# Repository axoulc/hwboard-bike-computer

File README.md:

# HWBoard Bike Computer PCB

This repository contains the KiCad hardware design for an open-source bike computer PCB. The target design is a solderable, small-series-friendly board with a sunlight-readable display, dual-frequency GNSS, BLE/ANT+ radio support, local storage, outdoor sensors, and USB-C rechargeable Li-ion power.

The hardware direction is based on a Rust `no_std` firmware target using `embassy-stm32`.

## Hardware Architecture

```text
USB-C 5 V
   |
   +-- ESD protection / CC resistors
   |
BQ25622E Li-ion charger with power path
   |
   +-- 1S Li-ion battery + NTC
   +-- SYS rail
   +-- I2C to STM32
        |
        +-- 3V3 system rail
        +-- low-noise GNSS rail
        +-- filtered radio rail
        +-- sensor rail
        +-- display backlight driver

STM32H563VIT6
   +-- SPI TFT display
   +-- I2C touch / sensors / power management
   +-- u-blox NEO-F10N GNSS over UART
   +-- nRF52840 module over SPI
   +-- microSD over SDMMC 4-bit
   +-- USB FS optional
   +-- SWD debug
```

## Main Components

| Function | Selected or target part | Notes |
|---|---|---|
| MCU | `STM32H563VIT6` | Cortex-M33, 250 MHz, 2 MB flash, 640 KB RAM, LQFP100 |
| GNSS | `u-blox NEO-F10N` | Dual-frequency L1/L5 GNSS with external active antenna |
| Radio | Raytac `MDBT50Q-U1MV2` module | nRF52840 module candidate with U.FL connector for an external antenna |
| Charger / power path | `BQ25622E` / `BQ25622ERYKR` | 1S Li-ion, USB-C input, I2C control |
| Fuel gauge | `MAX17048G+` | ModelGauge battery SoC monitor over I2C |
| Boost converter | `TPS61089` | High-current boost converter for auxiliary rails |
| IMU | `LSM6DSVTR` | 6-axis accelerometer + gyroscope |
| Magnetometer | `LIS2MDLTR` | Keep away from inductors, speaker/haptic parts, battery current, USB-C, and steel hardware |
| Barometer | `LPS22DFTR` preferred, `LPS22HBTR` acceptable | New design should prefer LPS22DF; include a vent and hydrophobic membrane |
| Storage | microSD | SDMMC 4-bit interface |
| Display | 2.8-3.0 inch 240x400 SPI TFT target | Final outdoor transflective panel still to be confirmed |

## Design Priorities

- No BGA packages for the main board.
- External antennas through U.FL / I-PEX MHF connectors.
- Keep GNSS, radio, magnetometer, switching converters, and backlight physically separated.
- Use a compact, well-controlled power layout around charger and boost switch nodes.
- Keep the display SPI bandwidth realistic by using partial redraws and DMA.
- Include physical buttons because touch can be unreliable with rain, gloves, or vibration.

## Documentation

Local component datasheets are kept in [docs/datasheets](docs/datasheets). The index in [docs/README.md](docs/README.md) records each local PDF and the official source URL.

Current local datasheets include:

- `STM32H563VI`
- `NEO-F10N`
- `MDBT50Q-U1MV2`
- `BQ25622E`
- `TPS61089`
- `LIS2MDL`
- `LSM6DSV`
- `LPS22DF`

The `MAX17048/MAX17049` datasheet is linked from the docs index through Analog Devices because the official PDF endpoint did not complete an unattended download in this environment.

## Preview

### Schematics

[Fullscreen PDF](https://axoulc.github.io/hwboard-bike-computer/assets/schematics/hwboard-bike-computer-schematic.pdf)

### PCB

#### Top

#### Bottom

### 3D

## Manufacturing

This project uses KiBot automation to generate manufacturing files:

- Schematics in PDF and PNG
- PCB documentation in PDF and PNG
- Bill of materials in HTML, XLSX, and interactive formats
- Gerbers, drill files, and position files
- 3D models and renders

See [KIBOT_CICD.md](KIBOT_CICD.md) for details.

## Sponsor

Thanks to PCBWay for sponsoring fabrication and assembly of the hwboard-bike-computer prototype.

## License

This project is licensed under the CERN Open Hardware Licence Version 2 - Permissive.

For more details, see <https://ohwr.org/project/cernohl/wikis/Documents/CERN-OHL-version-2>.

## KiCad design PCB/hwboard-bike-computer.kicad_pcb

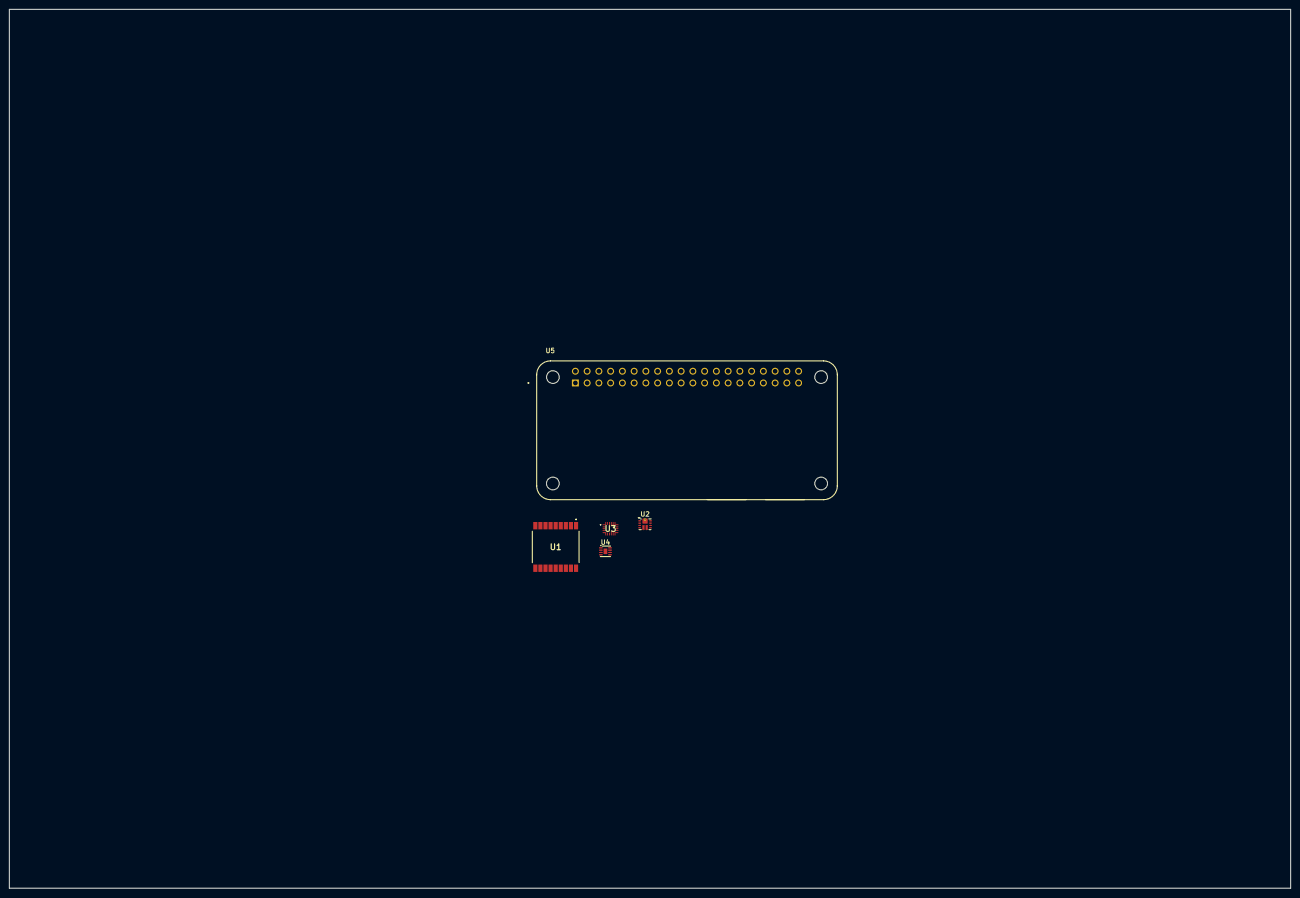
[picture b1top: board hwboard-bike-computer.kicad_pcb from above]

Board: 2 copper layers, 277.0 x 190.0 mm, 5 parts (0 on the bottom side), 6 nets, no tracks yet.

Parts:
U1: TESEO-LIV3R; TESEOLIV3R
U2: TPS61089; Texas_VQFN-RNR0011A-11
U3: BQ25622ERYKR
U4: MAX17048G+; TDFN-8-1EP_2x2mm_P0.5mm_EP0.8x1.2mm
U5: RASPBERRY_PI_ZERO_2_W; MODULE_RASPBERRY_PI_ZERO_2_W

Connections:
/CPU/3V3_{OUT}: U5.1 (3V3_1), U5.17 (3V3_17)
/CPU/5V_{IN}: U5.2 (5V_2), U5.4 (5V_4)
/Power Management/V_{BATT}: U3.8 (BAT), U4.2 (CELL), U4.3 (VDD)
/Power Management/V_{LOAD}: U2.9 (VIN), U3.9 (SYS)
GND: U1.1 (GND), U1.10 (GND_{RF}), U1.12 (GND_{RF}), U2.5 (GND), U3.15 (GND), U4.1 (CTG), U4.4 (GND), U4.6 (QSTRT), U4.9 (EP), U5.6 (GND_6), U5.9 (GND_9), U5.14 (GND_14), U5.20 (GND_20), U5.25 (GND_25), U5.30 (GND_30), U5.34 (GND_34), U5.39 (GND_39)
unnamed: U1.6 (V_{BATT}), U1.7 (VCC_{IO}), U1.8 (VCC)

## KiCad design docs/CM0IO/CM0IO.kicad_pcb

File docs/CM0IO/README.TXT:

These files have been created in version 9 of KiCAD.

Some of the 3d models need to be downloaded form the following places and put into the CM4IO.3dshapes directory some models are approximations.

https://www.molex.com/molex/products/part-detail/memory_card_socket/5033981892
https://www.molex.com/en-us/products/part-detail/2086581051

The models provided in the 3dmodels directory are from various manufacturers including RaspberryPi, Hirose. Terms and conditions for the use of the models remain with the original manufacture.

The CM0 model has the following license :

= Disclaimer =
These 3D models are provided under the MIT license included at the end of this file. The 3D models may incorporate individual 3D models that have been provided by third parties with permission to redistribute. No additional license terms are imposed by this use of third party provided 3D models, where applicable.

The overall 3D model and any individual 3D models incorporated into the whole, whether created by first or a third party, are provided here for guidance only and without guarantee of accuracy. Additionally, provided 3D model data may not reflect the most current version(s). Any third party intending to use the provided 3D model for appearance and fitment purposes must refer to manufacturer information and conduct suitable measurements of the physical product.

= MIT License =
Copyright (c) 2025 Raspberry Pi Ltd

Permission is hereby granted, free of charge, to any person obtaining a copy of this software and associated documentation files (the "Software"), to deal in the Software without restriction, including without limitation the rights to use, copy, modify, merge, publish, distribute, sublicense, and/or sell copies of the Software, and to permit persons to whom the Software is furnished to do so, subject to the following conditions:

The above copyright notice and this permission notice shall be included in all copies or substantial portions of the Software.

THE SOFTWARE IS PROVIDED "AS IS", WITHOUT WARRANTY OF ANY KIND, EXPRESS OR IMPLIED, INCLUDING BUT NOT LIMITED TO THE WARRANTIES OF MERCHANTABILITY, FITNESS FOR A PARTICULAR PURPOSE AND NONINFRINGEMENT. IN NO EVENT SHALL THE AUTHORS OR COPYRIGHT HOLDERS BE LIABLE FOR ANY CLAIM, DAMAGES OR OTHER LIABILITY, WHETHER IN AN ACTION OF CONTRACT, TORT OR OTHERWISE, ARISING FROM, OUT OF OR IN CONNECTION WITH THE SOFTWARE OR THE USE OR OTHER DEALINGS IN THE SOFTWARE.

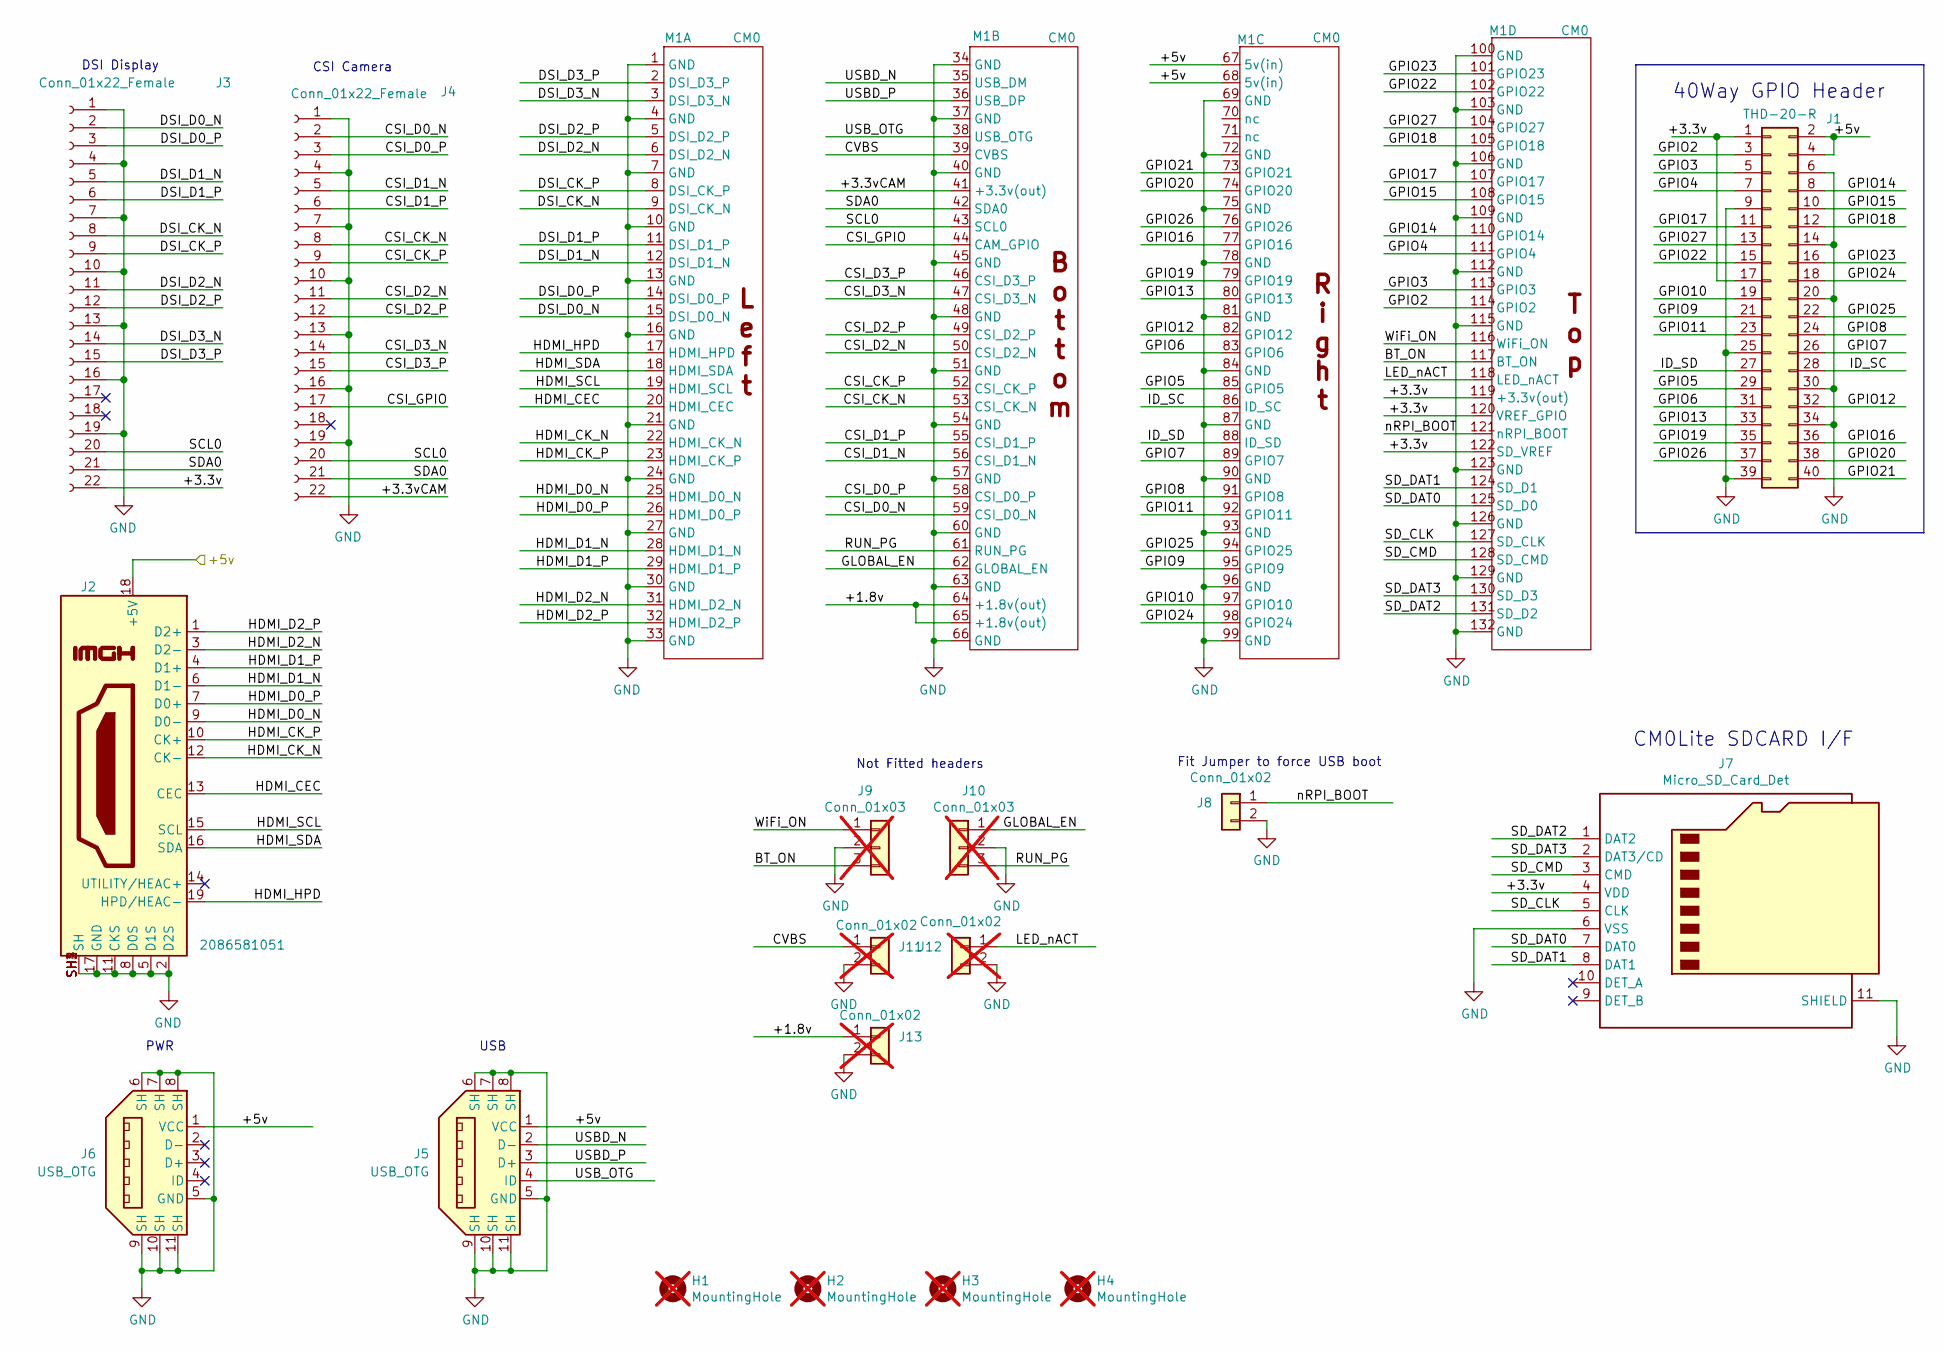
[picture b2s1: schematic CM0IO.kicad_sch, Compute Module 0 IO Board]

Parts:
H1, H2, H3, H4: MountingHole; MountingHole_2.7mm_M2.5; Part Description M2.5 mounting hole; not fitted
J1: THD-20-R; PinHeader_2x20_P2.54mm_Vertical; Part Description PinHeader_2x20_P2.54mm_Vertical
J2: 2086581051; Molex_2086581051; Part Description HDMI Connector, Right Angle, 19 Contact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
J3, J4: Conn_01x22_Female; Hirose_FH12-22S-0.5SH_1x22-1MP_P0.50mm_Horizontal; Part Description 22 Position FFC, FPC Connector Contacts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
J5, J6: USB_OTG; amphenol_10103594-0001lf; Part Description USB - micro B USB 2.0 Receptacle Connec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
J7: Micro_SD_Card_Det; SDCARD_MOLEX_503398-1892; Part Description 9 (8 + 1) Position Card Connector micro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
J8: Conn_01x02; PinHeader_1x02_P2.54mm_Vertical
J9, J10: Conn_01x03; PinHeader_1x03_P2.54mm_Vertical; Part Description 3pin 0.1" connector; not fitted
J11, J12, J13: Conn_01x02; PinHeader_1x02_P2.54mm_Vertical; not fitted
M1: CM0; Part Description Compute Module 0

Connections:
/+1.8v: J13.1, M1.64 (+1.8v(out)), M1.65 (+1.8v(out))
/+3.3v: J1.1, J1.17, J3.22, J7.4 (VDD), M1.119 (+3.3v(out)), M1.120 (VREF_GPIO), M1.122 (SD_VREF)
/+3.3vCAM: J4.22, M1.41 (+3.3v(out))
/+5v: J1.2, J1.4, J2.18 (+5V), J5.1 (VCC), J6.1 (VCC), M1.67 (5v(in)), M1.68 (5v(in))
/BT_ON: J9.3, M1.117 (BT_ON)
/CSI_CK_N: J4.8, M1.53 (CSI_CK_N)
/CSI_CK_P: J4.9, M1.52 (CSI_CK_P)
/CSI_D0_N: J4.2, M1.59 (CSI_D0_N)
/CSI_D0_P: J4.3, M1.58 (CSI_D0_P)
/CSI_D1_N: J4.5, M1.56 (CSI_D1_N)
/CSI_D1_P: J4.6, M1.55 (CSI_D1_P)
/CSI_D2_N: J4.11, M1.50 (CSI_D2_N)
/CSI_D2_P: J4.12, M1.49 (CSI_D2_P)
/CSI_D3_N: J4.14, M1.47 (CSI_D3_N)
/CSI_D3_P: J4.15, M1.46 (CSI_D3_P)
/CSI_GPIO: J4.17, M1.44 (CAM_GPIO)
/CVBS: J11.1, M1.39 (CVBS)
/DSI_CK_N: J3.8, M1.9 (DSI_CK_N)
/DSI_CK_P: J3.9, M1.8 (DSI_CK_P)
/DSI_D0_N: J3.2, M1.15 (DSI_D0_N)
/DSI_D0_P: J3.3, M1.14 (DSI_D0_P)
/DSI_D1_N: J3.5, M1.12 (DSI_D1_N)
/DSI_D1_P: J3.6, M1.11 (DSI_D1_P)
/DSI_D2_N: J3.11, M1.6 (DSI_D2_N)
/DSI_D2_P: J3.12, M1.5 (DSI_D2_P)
/DSI_D3_N: J3.14, M1.3 (DSI_D3_N)
/DSI_D3_P: J3.15, M1.2 (DSI_D3_P)
/GLOBAL_EN: J10.1, M1.62 (GLOBAL_EN)
/GPIO2: J1.3, M1.114 (GPIO2)
/GPIO3: J1.5, M1.113 (GPIO3)
/GPIO4: J1.7, M1.111 (GPIO4)
/GPIO5: J1.29, M1.85 (GPIO5)
/GPIO6: J1.31, M1.83 (GPIO6)
/GPIO7: J1.26, M1.89 (GPIO7)
/GPIO8: J1.24, M1.91 (GPIO8)
/GPIO9: J1.21, M1.95 (GPIO9)
/GPIO10: J1.19, M1.97 (GPIO10)
/GPIO11: J1.23, M1.92 (GPIO11)
/GPIO12: J1.32, M1.82 (GPIO12)
/GPIO13: J1.33, M1.80 (GPIO13)
/GPIO14: J1.8, M1.110 (GPIO14)
/GPIO15: J1.10, M1.108 (GPIO15)
/GPIO16: J1.36, M1.77 (GPIO16)
/GPIO17: J1.11, M1.107 (GPIO17)
/GPIO18: J1.12, M1.105 (GPIO18)
/GPIO19: J1.35, M1.79 (GPIO19)
/GPIO20: J1.38, M1.74 (GPIO20)
/GPIO21: J1.40, M1.73 (GPIO21)
/GPIO22: J1.15, M1.102 (GPIO22)
/GPIO23: J1.16, M1.101 (GPIO23)
/GPIO24: J1.18, M1.98 (GPIO24)
/GPIO25: J1.22, M1.94 (GPIO25)
/GPIO26: J1.37, M1.76 (GPIO26)
/GPIO27: J1.13, M1.104 (GPIO27)
/HDMI_CEC: J2.13 (CEC), M1.20 (HDMI_CEC)
/HDMI_CK_N: J2.12 (CK-), M1.22 (HDMI_CK_N)
/HDMI_CK_P: J2.10 (CK+), M1.23 (HDMI_CK_P)
/HDMI_D0_N: J2.9 (D0-), M1.25 (HDMI_D0_N)
/HDMI_D0_P: J2.7 (D0+), M1.26 (HDMI_D0_P)
/HDMI_D1_N: J2.6 (D1-), M1.28 (HDMI_D1_N)
/HDMI_D1_P: J2.4 (D1+), M1.29 (HDMI_D1_P)
/HDMI_D2_N: J2.3 (D2-), M1.31 (HDMI_D2_N)
/HDMI_D2_P: J2.1 (D2+), M1.32 (HDMI_D2_P)
/HDMI_HPD: J2.19 (HPD/HEAC-), M1.17 (HDMI_HPD)
/HDMI_SCL: J2.15 (SCL), M1.19 (HDMI_SCL)
/HDMI_SDA: J2.16 (SDA), M1.18 (HDMI_SDA)
/ID_SC: J1.28, M1.86 (ID_SC)
/ID_SD: J1.27, M1.88 (ID_SD)
/LED_nACT: J12.1, M1.118 (LED_nACT)
/RUN_PG: J10.3, M1.61 (RUN_PG)
/SCL0: J3.20, J4.20, M1.43 (SCL0)
/SDA0: J3.21, J4.21, M1.42 (SDA0)
/SD_CLK: J7.5 (CLK), M1.127 (SD_CLK)
/SD_CMD: J7.3 (CMD), M1.128 (SD_CMD)
/SD_DAT0: J7.7 (DAT0), M1.125 (SD_D0)
/SD_DAT1: J7.8 (DAT1), M1.124 (SD_D1)
/SD_DAT2: J7.1 (DAT2), M1.131 (SD_D2)
/SD_DAT3: J7.2 (DAT3/CD), M1.130 (SD_D3)
/USBD_N: J5.2 (D-), M1.35 (USB_DM)
/USBD_P: J5.3 (D+), M1.36 (USB_DP)
/USB_OTG: J5.4 (ID), M1.38 (USB_OTG)
/WiFi_ON: J9.1, M1.116 (WiFi_ON)
/nRPI_BOOT: J8.1, M1.121 (nRPI_BOOT)
GND: J1.6, J1.9, J1.14, J1.20, J1.25, J1.30, J1.34, J1.39, J2.2 (D2S), J2.5 (D1S), J2.8 (D0S), J2.11 (CKS), J2.17 (GND), J2.SH1 (SH), J2.SH2 (SH), J2.SH3 (SH), J2.SH4 (SH), J3.1, J3.4, J3.7, J3.10, J3.13, J3.16, J3.19, J4.1, J4.4, J4.7, J4.10, J4.13, J4.16, J4.19, J5.5 (GND), J5.6 (SH), J5.7 (SH), J5.8 (SH), J5.9 (SH), J5.10 (SH), J5.11 (SH), J6.5 (GND), J6.6 (SH), J6.7 (SH), J6.8 (SH), J6.9 (SH), J6.10 (SH), J6.11 (SH), J7.6 (VSS), J7.11 (SHIELD), J8.2, J9.2, J10.2, J11.2, J12.2, J13.2, M1.1 (GND), M1.4 (GND), M1.7 (GND), M1.10 (GND), M1.13 (GND), M1.16 (GND), M1.21 (GND), M1.24 (GND), M1.27 (GND), M1.30 (GND), M1.33 (GND), M1.34 (GND), M1.37 (GND), M1.40 (GND), M1.45 (GND), M1.48 (GND), M1.51 (GND), M1.54 (GND), M1.57 (GND), M1.60 (GND), M1.63 (GND), M1.66 (GND), M1.69 (GND), M1.72 (GND), M1.75 (GND), M1.78 (GND), M1.81 (GND), M1.84 (GND), M1.87 (GND), M1.90 (GND), M1.93 (GND), M1.96 (GND), M1.99 (GND), M1.100 (GND), M1.103 (GND), M1.106 (GND), M1.109 (GND), M1.112 (GND), M1.115 (GND), M1.123 (GND), M1.126 (GND), M1.129 (GND), M1.132 (GND)

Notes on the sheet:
40Way GPIO Header
Fit Jumper to force USB boot
USB
PWR
CSI Camera
CM0Lite SDCARD I/F
Not Fitted headers
DSI Display

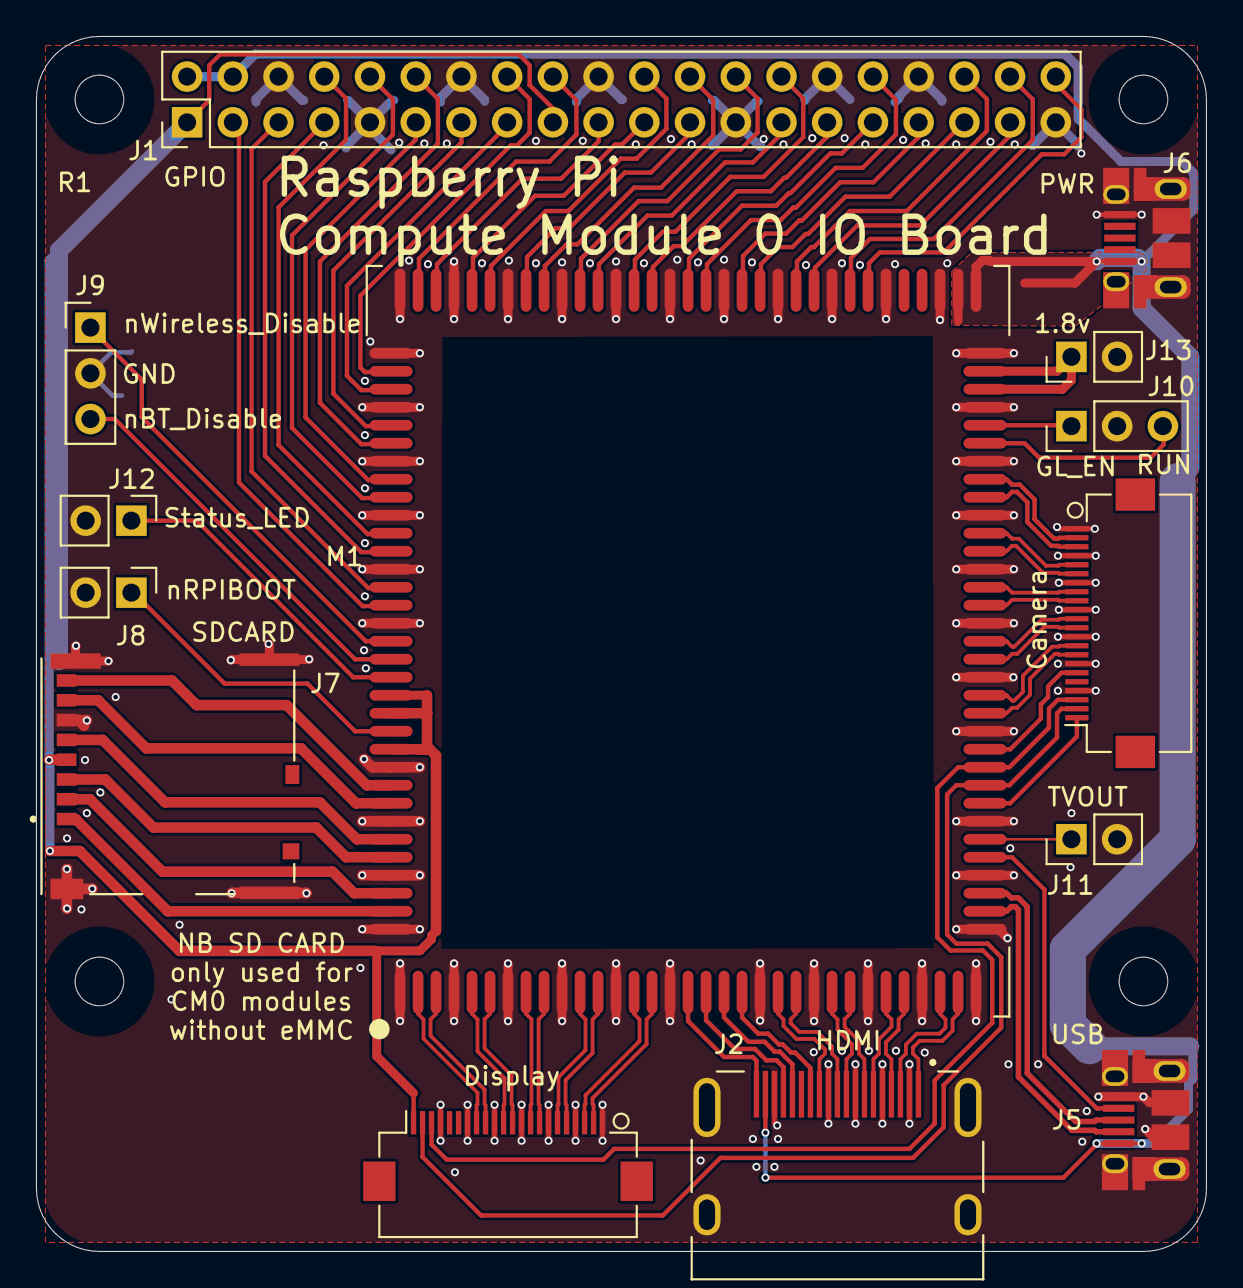
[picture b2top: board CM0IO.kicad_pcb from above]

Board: 2 copper layers, 65.0 x 67.5 mm, 18 parts (0 on the bottom side), 84 nets.

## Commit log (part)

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2025-10-14 remove project description file from GitHub repository
2025-10-14 Add CI/CD configuration and documentation for KiBot automation
    - Implement KiBot CI/CD workflow in .github/workflows/kibot.yml
    - Create issue and pull request templates for CI/CD issues
    - Update README.md with project details and quick start guide
    - Add KIBOT_CICD.md for comprehensive CI/CD documentation
    - Introduce Makefile for KiBot automation commands
    - Establish .gitignore for build artifacts and temporary files
2025-10-14 Update KiBot action version to v2_k9 in CI/CD workflow
2025-10-14 fix: Update file paths to PCB subdirectory in CI/CD workflow
    - Fixed schema and board paths in .github/workflows/kibot.yml
    - Updated Makefile to reference correct PCB file locations
    - Added CICD_FIX.md documenting the issue and resolution
    The KiCad files are located in PCB/ subdirectory, not in root.
    This fix ensures the CI/CD workflow can locate and process the files correctly.
2025-10-14 feat: Add initial KiCad project files for hwboard-bike-computer
2025-10-14 Remove temporary and configuration files related to the bike computer project, including lock, PCB, PRL, and project files.
2025-10-15 feat: Enhance CI/CD workflow for KiBot with GitHub Pages support and asset organization
2025-10-15 feat: Add PDF to PNG conversion step in CI/CD workflow
2025-10-15 feat: Update README with schematic and PCB previews
2025-10-22 feat: Update README with license, KiCad version, and PCB manufacturing sponsor details
2025-10-22 feat: Update README to include manufacturing sponsor and enhance PCB section
2025-10-22 add gnss schematics and footprint
2025-10-23 add screen sheet
2025-10-23 add others hierarchicals sheets
2025-10-24 add dc dc schematic
2025-10-24 add boost components
2025-10-27 add charger and fuel gauge ic
2025-10-27 schematic for charger and fuel gauge
2025-10-27 Update with gnss
2026-01-21 add sensors
2026-01-22 add sensors components
2026-02-10 add resistive touch IC
2026-03-06 add maybe layout and pcb for screen
2026-06-18 Major change CPU and usage
2026-06-18 change readme
2026-06-18 chenge kicad version
2026-06-18 change filname
2026-06-29 change of MCU and pins choosing
2026-06-29 Add new datasheets for Raytac MDBT50Q, STM32H563VI, and TPS61089

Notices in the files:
README.md:
License: CERN-OHL-P
docs/CM0IO/CM0IO.kicad_sch:
© 2025 Raspberry Pi Ltd
